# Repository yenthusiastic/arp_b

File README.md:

# Hochschule Rhein-Waal Applied Research Project WS19/20
## Project: Bikota - Distributed ledger-based bike renting system
##### Supervised by Prof. Timo Kahl
##### Group members: Andreas Markwart, Francisco-Alberto Susana-Canela, Thi Yen Thu Nguyen, Sarah-Maria Rostalski, Nader Kaake

### Problem Statement & Market Research 

Bike renting services are re-gaining popularity in many big cities around the world for short distances. Multiple renting services now allow users to conveniently locate vehicles with apps on their smartphone, initiate the renting and returning of a vehicle from and to anywhere unlike with the traditional renting stations.. 
However, current popular bike renting apps such as [Nextbike](https://www.nextbike.de/en/information/), [Lyft](https://www.lyft.com/bikes) or [Uber JUMP](https://www.jump.com/de/de/) require users to register and provide their private payment details. 

This project thus proposes an innovative bike renting service concept based on pseudo-anonymous, registration-free payment using Distributed Ledger Technology, namely [IOTA](https://www.iota.org/get-started/what-is-iota). IOTA is a permissionless, immutable, scalable ledger system that allows for feeless data transaction with or without monetary values. Hence, all data related to any renting session can be anonymously collected, analyzed and utilized for future improvements of the system.

### Methodology 
The architecture of the system (see Fig. 1) can be divided into three main elements, which are: the server that manages our service; the hardware that connects the bike to our platform; and the IOTA Node that processes the payments. Every element communicates with each other through HTTP protocol to process the request from the users and bike administrators. The server consists of three sub-elements or sub-servers which handle a particular task of the renting process such as API calls, data storage and the web platforms.

*Fig. 1: System architecture - BIKOTA Renting System*

### Implementation 
#### Hardware and Firmware
The hardware is based on an ESP32 microcontroller using an E-ink display for user interaction. A SIM800 module provides 2G mobile internet access. The firmware on the ESP32 is developed in the MicroPython programming language. Environmental data like temperature, relative humidity, atmospheric pressure, particulate matter (PM10, PM2.5) and CO2 are measured by multiple sensors. A GPS module provides location data, while an accelerometer is used for automated hardware wake up and vandalism detection.

#### Software 
The software frameworks for the BIKOTA bike renting system are separated into backend and frontend modules. The backend is based on a NodeJS server which implements a RESTful API application for receiving HTTP requests from the hardware modules and sending back responses correspondingly. The data received by the API is saved in a PostgreSQL database and represented visually using the frontend. 

The frontend again consists of two separate user interfaces: a landing page for the common user and a dashboard panel for the admin of the renting system. The web servers are implemented in Python using a Flask framework for web routing and HTTPS request handling.

### Results & Discussion
#### Hardware
The hardware module (see Fig. 2) is able to collect and publish geo-referenced data about its environment, which are sent via 2G to the API application at the backend. Each renting session is handled by the device itself, as the device is checking, if there is a positive balance for an IOTA address and displays the corresponding renting time on the E-ink display. In addition, due to the modular design, it is possible to use the device only for renting and tracking; the environmental sensors are optional.

*Fig. 2: BIKOTA hardware prototype*

#### Software
##### REST API
The REST API accepts the following types of requests from the hardware modules: asking for a new session address, sending sensor data, updating the hardware status. The API returns meaningful HTTP status codes to all requests to indicate whether the requests are successful or erroneous. The complete description of the REST API can be found [here](documentation/REST_API_Server.md).

##### Landing page
The [landing page](http://bikota.xyz) is responsive and can be accessed via computer or mobile phone. It gives the user the opportunity to locate available bikes nearby (see Fig. 3) and gives information about the renting process. After a renting session the user can also view the sensor data, which has been collected during the session, by entering the session address into the interface. The data of the environmental sensors will be displayed as charts and GPS data will be projected to a map.

*Fig. 3: Bike finder section of BIKOTA landing page*

##### Admin Panel
The [admin panel](http://admin.bikota.xyz) allows the admin to have an overview of all hardware modules in the system, including their locations, their status and their usage. The admin can also perform CRUD operations to the PostgreSQL database to create, read, update and delete hardware modules (see Fig. 4). Additionally, any sensor data collected by the hardware modules can also be visualized as graphs for environmental data monitoring. The complete description and usage manual of the admin panel can be found [here](documentation/Admin_Panel_Manual.md).

*Fig. 4: Hardware manager section of BIKOTA admin panel*

### Outlook
This project proposes a proof-of-concept for a bike renting system based on the IOTA ledger. The geo-referenced data as well as sensor data collected from renting sessions are stored and visualized but can be further analyzed for environmental monitoring purposes. For future work, the data can be sent to the IOTA Tangle using Masked Authenticated Messaging protocol to allow customizable distribution channels depending on the use cases, as well as data trading on the [IOTA Data Marketplace](https://data.iota.org/). 
Improvements can also be made to the hardware to automatically make a call or send an SMS once a collision or vandalism is detected to notify the bike owners immediately such that faster actions can be taken.

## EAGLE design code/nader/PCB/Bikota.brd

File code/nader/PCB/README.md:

# PCB development
This readme is going to describe the process of the PCB development. 
It is including the installation and configuration of KiCAD, the electrical and mechanical requirements for the PCB and the design process itself.

## Ideas & plans
The idea of this task is to develop a PCB, which is electrically connecting the single components (MCU, sensors, etc.) together. Most of the sensors are soldered on breakout boards, which include all electrical components necessary for a standard operation. These components are for example resistors, capacitors and/or voltage regulators. Most of the time, a pin header is also included in order to connect the sensor to the MCU using jumper wires.
Breakout boards have also the advantage, that they implicate a very good documentation and that they are easily reusable.
Of course, it is also possible to have a closer look at the breakout boards and use all the necessary components on the main PCB, which is going to be developed. But in order to reduce complexity and the time-stress-level, a PCB using the breakout boards is the way to go.

## Researches

### KiCAD vs. Eagle
The first decision to make is the question of the right PCB design software. The discussions are most of the time endless, but in the end, it is a question of personal preference, as both softwares have their advantages and disadvantages.

#### Price
KiCAD is free and open-source, which means that is possible to download the complete source code and modify it ad libitum. At the other side, EAGLE is available as a free version, but it is restricting the complexity of the projects by three different limitations:
* maximum of two layers
* maximum of two schematics sheets
* maximum of 80 cm² board size

It is also possible to use the full version of EAGLE, but it either costs 17.85 EUR monthly or 130.90 EUR yearly.

#### User interface / User experience
The user interfaces of both softwares are optically not feauturing any major differences, but in terms of user experience, KiCAD is one step ahead by including standard keyboard shortcuts for the different main tools you use when designing a PCB. With Eagle it is possible to use shortcuts, but with the difference, that they have to be configured first. Nevertheless, EAGLE is featuring a command line, where it is possible to type in commands (e.g. wire, place component, etc.). EAGLE's main advtange is that the process of developing a PCB is much more straight-forward, as it takes less steps:
1. Create a schematic
2. Place components. (Here, each time you place a component, you already define the type of footprint you want to choose)
3. Connect the components (circuit)
4. Generate board (one click and the components are placed on the edge of the board)
5. Final placements and connections are made (Changes in the schematics are directly copied in the board)

KiCad involves a few more steps, but after executing these steps multiple times, it does not make a difference. The difference is more decisive for a new-comer.
* The footprints of the components are selected after placing all the components in the schematic.
* Components are not directly named when getting placed
* The process of getting the components and connections to the board involves two more steps
    * Create a netlist
    * Load netlist into the board

#### Components organization
In every PCB design software, each single component is including a *footprint* and a *symbol*; KiCAD and EAGLE are not making any exceptions. The symbol is used when the component is placed in one of the schematics sheets, where rotation and position are not playing any roles. It is only important, that the component is placed and connected to the other components with the *wire tool*. As soon as the schematics are finished, it is time to place the footprint of the component. Here, the position as well as the roation are crucial, as the component is going to be soldered (or fixed) exactly how it is placed in the *Gerber files* (output files of the PCB).
Both softwares have a libary, where you can manage the symbols as well as the footprints, but in my opinion, the one of EAGLE is much more easier to handle. KiCAD is a little bit more complicated (as you can see under *Problems & Troubleshooting*).

### Components
* [LIS3DH](https://www.st.com/resource/en/datasheet/lis3dh.pdf) - Acceleration sensor
* [VIS3590](https://www.reichelt.de/12-mm-magnetischer-buzzer-vis-3590-p248314.html?PROVID=2788&gclid=Cj0KCQiAk7TuBRDQARIsAMRrfUZGc0MFfkMijM4triyhI70YJm8uVk0_bFY5iUcvsQDlfDWVVrutPQUaAqmwEALw_wcB&&r=1) - Buzzer
* [MH-Z14A](https://www.banggood.com/de/NDIR-CO2-Sensor-MH-Z14A-PWM-NDIR-Infrared-Carbon-Dioxide-Sensor-Module-Serial-Port-0-5000PPM-Controller-p-1248270.html?gmcCountry=DE&currency=EUR&createTmp=1&utm_source=googleshopping&utm_medium=cpc_bgs&utm_content=frank&utm_campaign=frank-ssc-de-css-all-19bf11&ad_id=380597671089&gclid=Cj0KCQiAk7TuBRDQARIsAMRrfUZKyH9uKiOI8AsN_9JS3UmNfRLCO_lH9K2vEJEZapdY7mxqP0jCGBUaArfyEALw_wcB&cur_warehouse=CN) - CO₂ sensor
* [BN220](https://www.banggood.com/de/Beitian-BN-220T-GPS-GLONASS-Module-For-APM-Pixhawk-CC3D-Naze32-F3-F4-Flight-Controller-RC-Drone-Airplane-p-1446169.html?gmcCountry=DE&currency=EUR&createTmp=1&utm_source=googleshopping&utm_medium=cpc_bgs&utm_content=frank&utm_campaign=ssc-de-all-0716&ad_id=367212437657&gclid=Cj0KCQiAk7TuBRDQARIsAMRrfUZp8J6SOXBwY3z7kkAh3ZLmuUUmqHAU2cbT82qMtKNmgjt5V-ikGVwaArADEALw_wcB&cur_warehouse=CN) - GPS sensor
* [SDS011](https://www.banggood.com/de/Geekcreit-Nova-PM-Sensor-SDS011-High-Precision-Laser-PM2_5-Air-Quality-Detection-Sensor-Module-Tester-p-1144246.html?gmcCountry=DE&currency=EUR&createTmp=1&utm_source=googleshopping&utm_medium=cpc_bgs&utm_content=frank&utm_campaign=frank-ssc-de-css-all-19bf11&ad_id=380597671089&gclid=Cj0KCQiAk7TuBRDQARIsAMRrfUaDJpclHDIj_aa5fgJSP1aEasOmDeB9t93sI-2GWzTbn4nR9yIGIDQaAoamEALw_wcB&cur_warehouse=CN) - PM sensor
* [RND 135-00180](https://www.reichelt.de/led-smd-0603-blau-200-mcd-rnd-135-00180-p263776.html?&trstct=pol_8) - Status LED
* [BME280](https://www.reichelt.de/entwicklerboards-temperatur-feuchtigkeits-und-drucksensor-debo-sens-thd-p235476.html?&trstct=pos_2) - Temperature, pressure and humidity sensor

## Development of the PCB
In this part, the hardware implementation is going to be outlined. In general, it is the part of the project where all modules with all necessary components are going to be connected to each other on one single place.

### Results
The PCB v0.1 has a final size of 83.69mm by 78.11mm. All sensors are connected to the microcontroller via the PCB, but as all environmental sensors are only used as soon as the bicycle is in use, they are switched on by a mosfet in order to save power. In addition, all the environmental sensors are connected via jumper cables to the board, due to the mounting on the housing because of airflow. 

#### Schematics
The following figure is showing the final schematics of the PCB in version 0.1. 

</br>

The big part in the middle of the schematic is the microcontroller (ESP32) itself. As this PCB is still some kind of a prototype, we have placed socket connector strips next to the connections of the MCU itself in order to have a direct access to all the necessary pins when debugging is necessary. The jumper JP6 is connected to a resistor, which is then directly connected to ground and used for a potential LED. The few components above the microcontroller are used for the buzzer, which is giving an accousting feedback whenever the device is swiched on. Additionally, it can be used to give a general accoustic feedback for different kinds of situations. The three components to the right of the MCU are the three environmental sensors. Above is the measuring the temperature, humidity and the pressure, while the middle one is the CO₂ sensor and below is the sensor used for the measurement of particulate matter in the air. The component in the lower right corner is the ePaper-module, which is displaying the QR-code and general information about the rental itself. Below of the MCU is a voltage divider, which is sent to the sensVN pin of the microcontroller. In the lower left corner is the circuit of the mosfet, which is switching the three environmental sensor on and off. The first component above the mosfet circuit is the voltage regulator including the power socket, which is providing the board with 5V with an input voltage of 3-5V. The GPS module is seen above the voltage regulator, while the last component in the upper left corner is the acceleration sensor itself. The accelerometer is the only sensor, which is soldered directly on the board instead of a connection via jumper wires. 

#### Layout
Once the schematics are finished, the PCB itself has to be designed. All connections are already defined, so it is necessary to place all components in a smart way in order to prevent long traces between two components and also route these traces. The figure below is showing the initial look of the PCB as soon as the file board is generated by the schematics. The yellow lines between the components are representing necessary connections, which have to be routed. In general one can say, that the more chaotic the lines are, the more chaotic is going to be the final routing. 
The first step is to place the components to their final positions, which is shown in the image below. The black area is representing the current dimensions of the PCB. Here, it is very helpful to first group components together. For example, in the schematics it can be seen that the circuit of the mosfet is including the transistor itself, three resistors and an LED. This means, that these components are at the best placed right next to each other. Another example are the spcker connector strips; These have to be placed next to the microcontroller, as its pins are directly connected to those of the sockets. 

</br>

The next figure is showing the PCB after the components have been placed. The power is coming through the connector in the upper left corner. The modules and sensors are placed corresponding to the position of the microcontroller's pins. That's why the ePaper display, the CO₂-Sensor and the GPS module are placed on one side, and the others (Accelerometer, PM-sensor, environmental-sensor and buzzer) are placed on the other side. Furthermore, the mounting houles of the PCB itself have also been placed in the four corners, which fit 3mm mounting screws. 

</br>

The following figure is illustrating the status of the board after the final step. 

</br>

### Problems & Troubleshooting

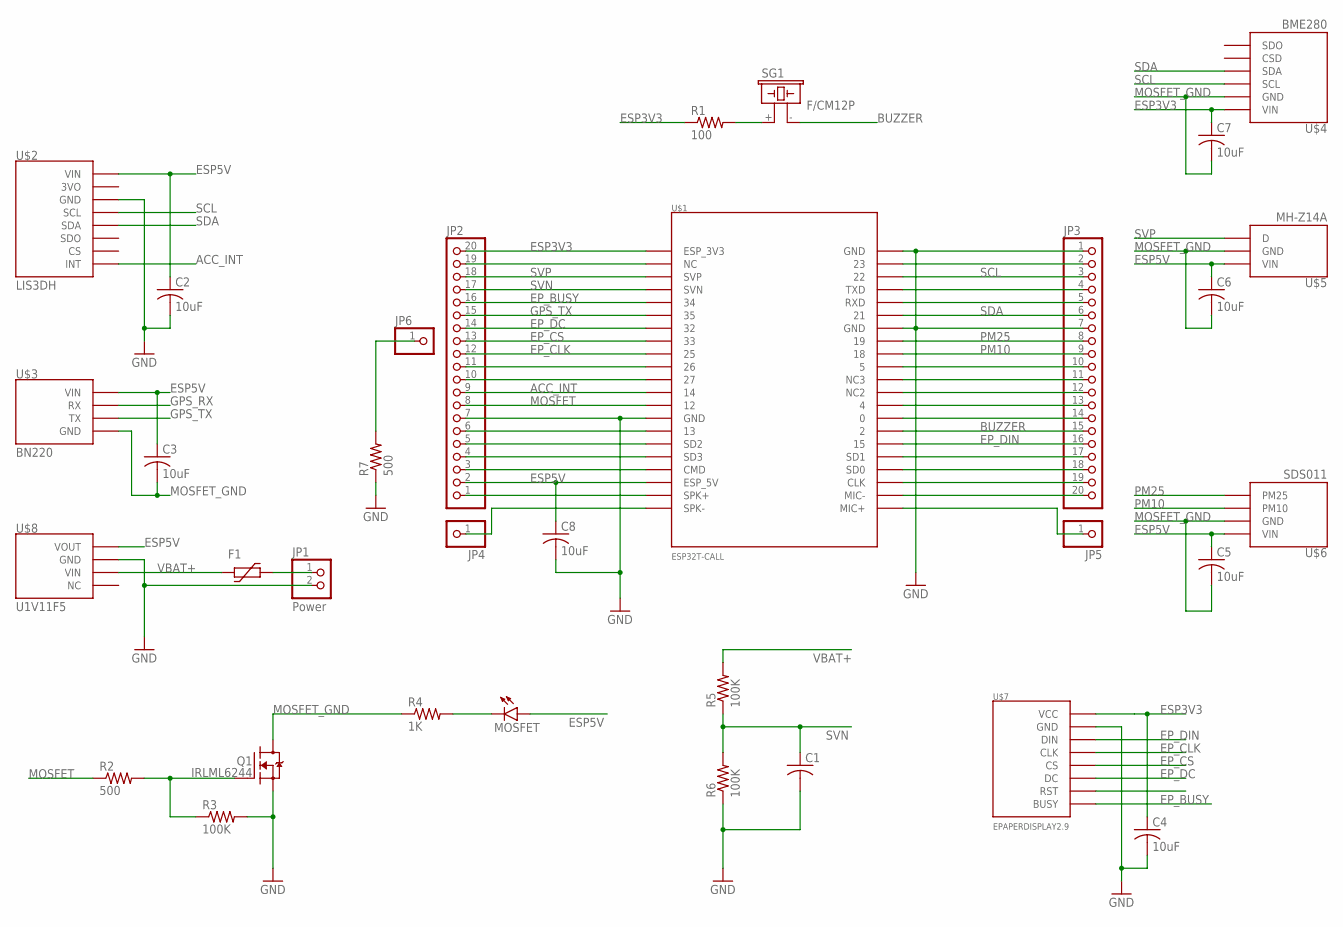
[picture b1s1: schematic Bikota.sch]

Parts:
C1: C-USC0805; C0805
C2, C3, C4, C5, C6, C7, C8: 10uF; C0805
F1: 1206L
JP1: Power; 1X02
JP2, JP3: PINHD-1X20; 1X20
JP4, JP5, JP6: PINHD-1X1; 1X01
MOSFET: LEDCHIPLED_0805; CHIPLED_0805
Q1: IRLML6244; SOT23
R1: 100; R0805
R2, R7: 500; R0805
R3, R5, R6: 100K; R0805
R4: 1K; R0805
SG1: F/CM12P
U$1: ESP32T-CALL
U$2: LIS3DH
U$3: BN220
U$4: BME280
U$5: MH-Z14A
U$6: SDS011
U$7: EPAPERDISPLAY2.9
U$8: U1V11F5

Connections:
3VO: U$2.P$2 (3VO)
ACC_INT: JP2.9, U$1.GPIO14 (14), U$2.P$8 (INT)
BUZZER: JP3.15, SG1.- (2), U$1.GPIO2 (2)
EP_BUSY: JP2.16, U$1.GPIO34 (34), U$7.P$8 (BUSY)
EP_CLK: JP2.12, U$1.GPIO25 (25), U$7.P$4 (CLK)
EP_CS: JP2.13, U$1.GPIO33 (33), U$7.P$5 (CS)
EP_DC: JP2.14, U$1.GPIO32 (32), U$7.P$6 (DC)
EP_DIN: JP3.16, U$1.GPIO15 (15), U$7.P$3 (DIN)
ESP3V3: C4.1, C7.1, JP2.20, R1.1, U$1.ESP32_3V3 (ESP_3V3), U$4.P$1 (VIN), U$7.P$1 (VCC)
ESP5V: C2.1, C3.1, C5.1, C6.1, C8.1, JP2.2, MOSFET.A, U$1.ESP32_5V (ESP_5V), U$2.P$1 (VIN), U$3.P$1 (VIN), U$5.P$1 (VIN), U$6.P$1 (VIN), U$8.P$1 (VOUT)
GND: C1.2, C2.2, C4.2, C8.2, JP1.2, JP2.7, JP3.1, JP3.7, Q1.2 (S), R3.2, R6.1, R7.1, U$1.GND, U$1.GND2 (GND), U$1.GND3 (GND), U$2.P$3 (GND), U$7.P$2 (GND), U$8.P$2 (GND)
GPS_RX: U$3.P$2 (RX)
GPS_TX: JP2.15, U$1.GPIO35 (35), U$3.P$3 (TX)
MOSFET: JP2.8, R2.1, U$1.GPIO12 (12)
MOSFET_GND: C3.2, C5.2, C6.2, C7.2, Q1.3 (D), R4.1, U$3.P$4 (GND), U$4.P$2 (GND), U$5.P$2 (GND), U$6.P$2 (GND)
unnamed: R1.2, SG1.+ (1)
unnamed: JP2.19, U$1.P$2 (NC)
unnamed: Q1.1 (G), R2.2, R3.1
unnamed: MOSFET.C, R4.2
unnamed: JP2.11, U$1.GPIO26 (26)
unnamed: JP2.10, U$1.GPIO27 (27)
unnamed: JP2.6, U$1.GPIO13 (13)
unnamed: JP2.5, U$1.SD2
unnamed: JP2.4, U$1.SD3
unnamed: JP2.3, U$1.CMD
unnamed: JP2.1, U$1.SPK+
unnamed: JP4.1, U$1.SPK-
unnamed: JP6.1, R7.2
unnamed: JP3.2, U$1.GPIO23 (23)
unnamed: JP3.4, U$1.TXD
unnamed: JP3.5, U$1.RXD
unnamed: JP3.10, U$1.GPIO5 (5)
unnamed: JP3.11, U$1.NC3
unnamed: JP3.12, U$1.NC2
unnamed: JP3.13, U$1.GPIO4 (4)
unnamed: JP3.14, U$1.GPIO0 (0)
unnamed: JP3.17, U$1.SD1
unnamed: JP3.18, U$1.SD0
unnamed: JP3.19, U$1.CLK
unnamed: JP3.20, U$1.MIC-
unnamed: JP5.1, U$1.MIC+
unnamed: F1.P$2 (2), JP1.1
PM10: JP3.9, U$1.GPIO18 (18), U$6.P$3 (PM10)
PM25: JP3.8, U$1.GPIO19 (19), U$6.P$4 (PM25)
SCL: JP3.3, U$1.GPIO22 (22), U$2.P$4 (SCL), U$4.P$3 (SCL)
SDA: JP3.6, U$1.GPIO21 (21), U$2.P$5 (SDA), U$4.P$4 (SDA)
SVN: C1.1, JP2.17, R5.1, R6.2, U$1.SVN
SVP: JP2.18, U$1.SVP, U$5.P$3 (D)
VBAT+: F1.P$1 (1), R5.2, U$8.P$3 (VIN)

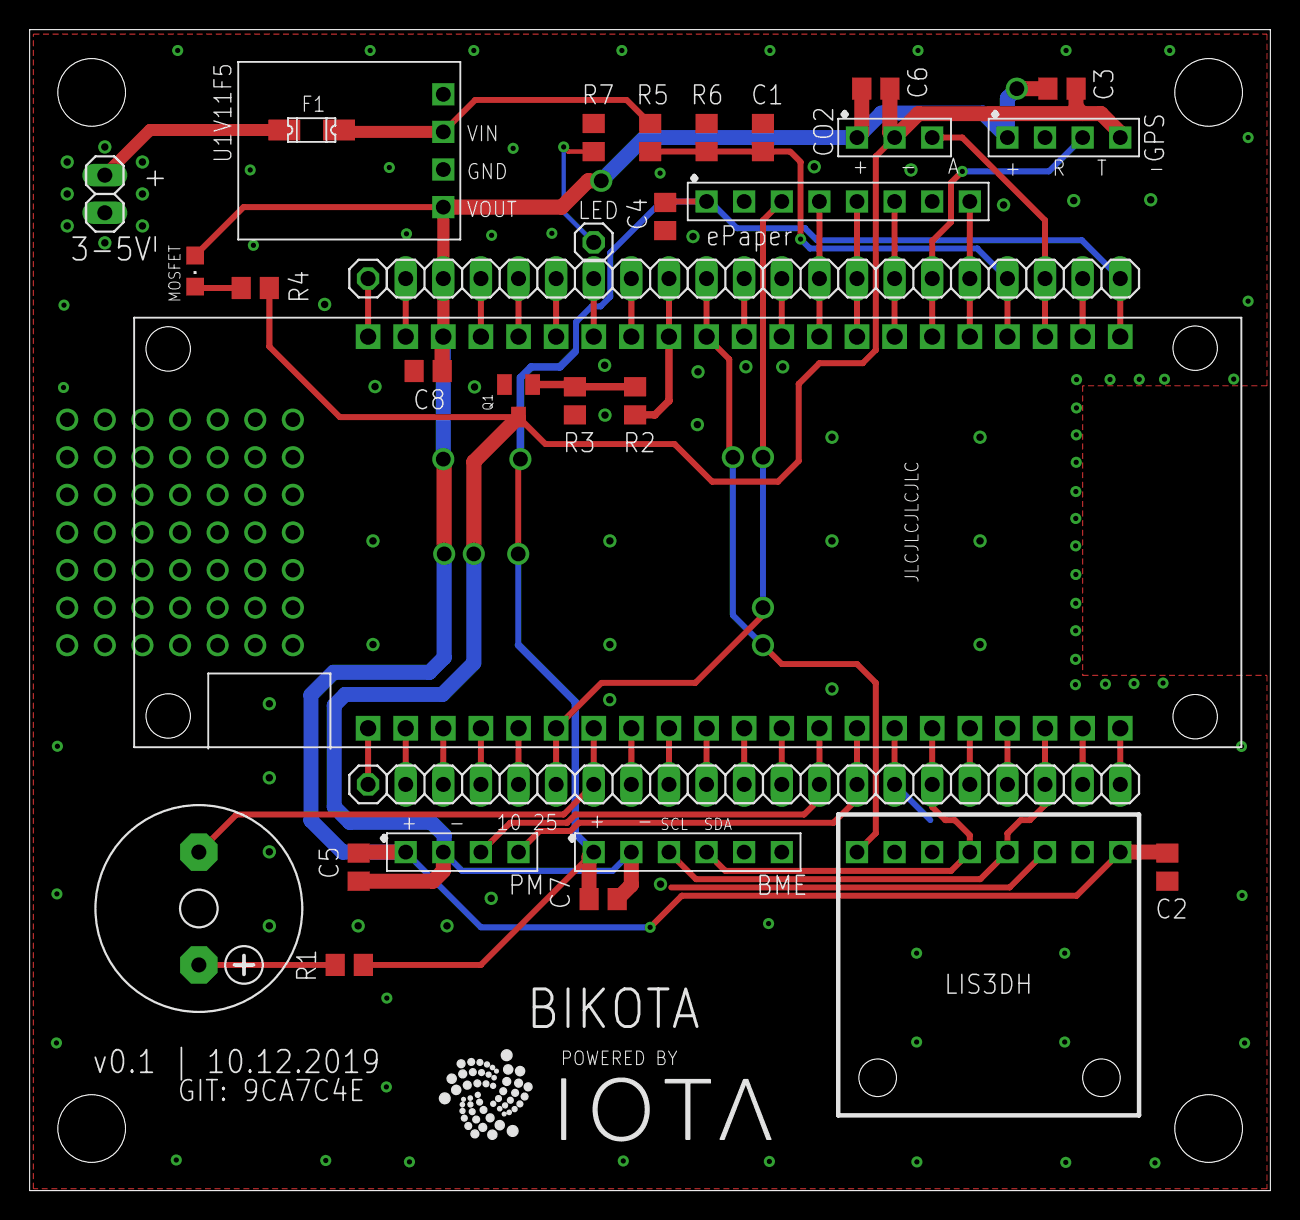
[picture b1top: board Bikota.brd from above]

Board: 2 copper layers, 83.8 x 78.4 mm, 33 parts (0 on the bottom side), 47 nets.

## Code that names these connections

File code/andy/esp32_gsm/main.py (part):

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

# Accelerometer Interrupt wake-up pin
acc_int = Pin(14, Pin.IN, Pin.PULL_DOWN)

# wake-up source for deepsleep
#rtc.wake_on_ext0(pin=btn1, level=0) #wakeup at btn low
rtc.wake_on_ext0(pin=acc_int, level=1) # wakeup at acc_int high

# MOSFET for 5V AUX
mos = Pin(12, Pin.OUT, value=0)
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

# PM sensor, SDS011
PM10_PIN = Pin(19, Pin.IN)
PM25_PIN = Pin(18, Pin.IN)


# Turn on auxiliary sensors
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    

"""
def get_pm(p10=PM10_PIN, p25=PM25_PIN):
    while p10.value() !=0:
        sleep_ms(1)
    while p10.value() == 0:
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"""

if SENSOR_MODE:
    def get_pm(p10=PM10_PIN, p25=PM25_PIN):
        while p10.value() == 0:
            pass
        st_10=ticks_ms()
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
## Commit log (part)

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2019-09-22 make directories
2019-09-22 make sub directories for each member's code
2019-09-22 add documentation for dev-server
2019-09-23 add gsm-module control, add RTC setup by NTP, fix get_balance()
2019-09-24 update Concept
2019-09-24 add directory 'sensors'
2019-09-24 add list of sensors to 'hardware'
2019-09-24 update esp32 modem and low-power operation documentation
2019-09-25 update power measurements
2019-09-25 update flashing instructions
2019-09-25 [thu] update to-dos list
2019-09-27 add function to send IOTA transaction containing sensor data from API server to IOTA node
2019-09-29 server file name update
2019-09-30 update documentation for API and DB requirements
2019-09-30 add main.py
2019-10-01 add arduino_gsm example
2019-10-01 update MicroPython binaries
2019-10-01 add AT-command based SIM800 library - in development
2019-10-06 add micropython at-command version
2019-10-06 refractor ESP32 code
2019-10-07 add new sub folders for members
2019-10-08 add sds011 library
2019-10-08 add sensor datasheets
2019-10-12 add DHT22, GPIO cleanup, test deepsleep wakeup
2019-10-12 add flask-dashboard template
2019-10-12 update postgres image to version 12
2019-10-12 Update API_DB_structure.md
    Correct database name.
2019-10-13 REST API V1.0, get & post http request
2019-10-14 Error handling added as described in API_DB_Structure.
2019-10-14 add library for QR code generation
2019-10-14 add display output, qr-code generation, mpu6050
2019-10-15 update info on messagepack
2019-10-16 modify mpu6050 library
2019-10-16 integrade epaper display
2019-10-17 Update app.js and queries.js files
2019-10-17 catch updated to catch(e)
2019-10-17 add notes for virtual environment
2019-10-17 Rquest update
2019-10-17 1.1-Fixing API response to python request
2019-10-18 modify for new b/w only e-paper
2019-10-18 add library for b/w only e-paper
2019-10-21 add functions for display update rate testing
2019-10-22 add MPU6050 datasheets
2019-10-24 add MZ-14 CO2 sensor
2019-10-30 add mpu6050 example for esp32 with oled
2019-10-31 add authentication and profile for admin interface
2019-10-31 add notifications for admin page
2019-11-01 add form controls for chart customization
2019-11-03 add more UI controls for web admin interface
    - add Date/Time Range Picker
    - allow multiple series per chart
2019-11-03 dynamic generation of charts based on user 's input
    - allow mutiple charts and mutilple series per chart to be plotted based on user's selections
    - TO DO: fix problem with slow database communication
2019-11-03 add BME280 library
2019-11-03 integrate BME280
2019-11-07 add toggle for editing modes, use bootstrap select library for dropdown menus
2019-11-09 add MOSFET and buzzer, add RTC-memory handling for status and address, streamline startup process, add startup sound
2019-11-10 save session_address and qr-code to RTC-memory and load at wakeup
2019-11-11 [Web UI] add new page for hardware manager
2019-11-12 finish basic hardware manager page
2019-11-14 Initial update
    - Sourcecode of the logical connection of MCU and Accelerometer (interrupts not working yet)
    - Driver for ESP32 (Win10)
    - ReadMe of the PCB development
2019-11-14 Delete README.md
    Separate READMEs in their specific folders
2019-11-17 Added Arduino Sketch File
    Interrupt configuration using the LIS3DH acceleration sensor.
    + interrupts are working and configurations settings are well tuned (thresholds, duration, etc.)
    - Wake-Up missing
2019-11-17 Update LIS3DH_INT.ino
    Added comments
2019-11-18 folder name update
2019-11-18 update package.json files
2019-11-18 Update comments and port var
2019-11-23 Status code for POST and PUT updated
2019-11-26 iota-api program to generate, and verify an address, and connect to test node
2019-11-28 fix Admin Panel bugs, create usage manual document
2019-11-29 update documentation for admin panel
2019-12-01 implement map page to show bike distribution
2019-12-01 update co2 sensor datasheet
2019-12-01 update documentation
2019-12-03 Added lis3dh file
    Driver and interrupt settings (accceleration values not available)
2019-12-06 Uploaded first version of the PCB
    Including Libraries and ULP to automatically create rectangles
2019-12-07 Added additional libraries
    Bikota.lbr is replacing lis3dh.lbr
2019-12-07 Updated schematic and board files.
2019-12-08 Refractoring: add constants
2019-12-08 Endpoints updated and IOTA-API integrated to generate seed and session address.
2019-12-08 app.js renamed and query-address.js logs display improved.
2019-12-08 Update on generate-seed.js the var 'randomValues' to Uint32Array
2019-12-09 Session_address added to the response on the query-address.
2019-12-09 Update PCB and SCH
2019-12-11 fix hardware.html to handle null data
2019-12-12 Update V0.1
    - put "3-5V" below the input socket
    - named the mosfet-led "MOSFET" instead of "LED1"
2019-12-12 Upload Gerber files
2019-12-13 Upload img of schematics
2019-12-13 Added images of the board
2019-12-21 RESTAPI: enable new hardware address query request.
2019-12-22 RESTAPI: code refactoring.
2019-12-22 lis3dh.py updated
    Changed/corrected functions to write registers of the accelerometer
2020-01-04 add get_address function; add LIS3DH Sensor; add battery voltage reading; fix parking and balance_update countdown
2020-01-04 add gitignore for code/andy
2020-01-05 add data aggregation function to chart page
2020-01-05 add wake-up by LIS3DH interrupt; add demo mode for session; streamline first boot
2020-01-06 RESTAPI: Code refactoring to optimize API routes and DB connection.
2020-01-06 show last sensor data on map
2020-01-08 Uploaded an image of the board
2020-01-09 add SENSOR_MODE flag for environmental sensors; add watchdog resets; fix backend keyword change
2020-01-12 Bump werkzeug from 0.14.1 to 0.15.3 in /code/thu/flask-dashboard
    Bumps [werkzeug](https://github.com/pallets/werkzeug) from 0.14.1 to 0.15.3.
    - [Release notes](https://github.com/pallets/werkzeug/releases)
    - [Changelog](https://github.com/pallets/werkzeug/blob/master/CHANGES.rst)
    - [Commits](https://github.com/pallets/werkzeug/compare/0.14.1...0.15.3)
2020-01-12 RESTAPI: add README file.
2020-01-12 RESTAPI: Fix readme file format.
2020-01-13 RESTAPI: Node status integration update.
2020-01-15 edit aggregation logic for chart data, fix JS logic for chart control dropdown menus
2020-01-16 RESTAPI: router update and data-post fixed.
2020-01-19 Webpage for user
2020-02-13 RESTAPI: readme update.
2020-02-13 update libraries
2020-02-14 REST API: README update.
2020-02-28 README update
2020-08-20 Bump bcrypt from 3.0.6 to 5.0.0 in /code/francisco/rest_api_server
    Bumps [bcrypt](https://github.com/kelektiv/node.bcrypt.js) from 3.0.6 to 5.0.0.
    - [Release notes](https://github.com/kelektiv/node.bcrypt.js/releases)
    - [Changelog](https://github.com/kelektiv/node.bcrypt.js/blob/master/CHANGELOG.md)
    - [Commits](https://github.com/kelektiv/node.bcrypt.js/compare/v3.0.6...v5.0.0)
2021-04-30 Bump urllib3 from 1.25.7 to 1.25.8 in /code/thu/flask-dashboard
    Bumps [urllib3](https://github.com/urllib3/urllib3) from 1.25.7 to 1.25.8.
    - [Release notes](https://github.com/urllib3/urllib3/releases)
    - [Changelog](https://github.com/urllib3/urllib3/blob/main/CHANGES.rst)
    - [Commits](https://github.com/urllib3/urllib3/compare/1.25.7...1.25.8)
2021-05-06 Bump flask-cors from 3.0.7 to 3.0.9 in /code/thu/flask-dashboard
    Bumps [flask-cors](https://github.com/corydolphin/flask-cors) from 3.0.7 to 3.0.9.
    - [Release notes](https://github.com/corydolphin/flask-cors/releases)
    - [Changelog](https://github.com/corydolphin/flask-cors/blob/master/CHANGELOG.md)
    - [Commits](https://github.com/corydolphin/flask-cors/compare/3.0.7...3.0.9)
2021-06-02 Bump urllib3 from 1.25.7 to 1.26.5 in /code/thu/flask-dashboard
    Bumps [urllib3](https://github.com/urllib3/urllib3) from 1.25.7 to 1.26.5.
    - [Release notes](https://github.com/urllib3/urllib3/releases)
    - [Changelog](https://github.com/urllib3/urllib3/blob/main/CHANGES.rst)
    - [Commits](https://github.com/urllib3/urllib3/compare/1.25.7...1.26.5)
    ---
    updated-dependencies:
2021-10-06 Bump url-parse from 1.4.7 to 1.5.3 in /code/francisco/rest_api_server
    Bumps [url-parse](https://github.com/unshiftio/url-parse) from 1.4.7 to 1.5.3.
    - [Release notes](https://github.com/unshiftio/url-parse/releases)
    - [Commits](https://github.com/unshiftio/url-parse/compare/1.4.7...1.5.3)
    ---
    updated-dependencies:
    - dependency-name: url-parse
2022-02-10 Bump undefsafe from 2.0.2 to 2.0.5 in /code/francisco/rest_api_server
    Bumps [undefsafe](https://github.com/remy/undefsafe) from 2.0.2 to 2.0.5.
    - [Release notes](https://github.com/remy/undefsafe/releases)
    - [Commits](https://github.com/remy/undefsafe/compare/v2.0.2...v2.0.5)
    ---
    updated-dependencies:
    - dependency-name: undefsafe
2022-02-18 Bump url-parse from 1.4.7 to 1.5.7 in /code/francisco/rest_api_server
    Bumps [url-parse](https://github.com/unshiftio/url-parse) from 1.4.7 to 1.5.7.
    - [Release notes](https://github.com/unshiftio/url-parse/releases)
    - [Commits](https://github.com/unshiftio/url-parse/compare/1.4.7...1.5.7)
    ---
    updated-dependencies:
    - dependency-name: url-parse
2022-03-29 Bump paramiko from 2.6.0 to 2.10.1 in /code/thu/flask-dashboard
    Bumps [paramiko](https://github.com/paramiko/paramiko) from 2.6.0 to 2.10.1.
    - [Release notes](https://github.com/paramiko/paramiko/releases)
    - [Changelog](https://github.com/paramiko/paramiko/blob/main/NEWS)
    - [Commits](https://github.com/paramiko/paramiko/compare/2.6.0...2.10.1)
    ---
    updated-dependencies:
2022-04-28 Bump cross-fetch from 3.0.4 to 3.1.5 in /code/francisco/rest_api_server
    Bumps [cross-fetch](https://github.com/lquixada/cross-fetch) from 3.0.4 to 3.1.5.
    - [Release notes](https://github.com/lquixada/cross-fetch/releases)
    - [Commits](https://github.com/lquixada/cross-fetch/compare/v3.0.4...v3.1.5)
    ---
    updated-dependencies:
    - dependency-name: cross-fetch
2022-09-16 Bump mako from 1.1.0 to 1.2.2 in /code/thu/flask-dashboard
    Bumps [mako](https://github.com/sqlalchemy/mako) from 1.1.0 to 1.2.2.
    - [Release notes](https://github.com/sqlalchemy/mako/releases)
    - [Changelog](https://github.com/sqlalchemy/mako/blob/main/CHANGES)
    - [Commits](https://github.com/sqlalchemy/mako/commits)
    ---
    updated-dependencies:
2022-12-07 Bump qs, body-parser and express in /code/francisco/rest_api_server
    Bumps [qs](https://github.com/ljharb/qs) to 6.11.0 and updates ancestor dependencies [qs](https://github.com/ljharb/qs), [body-parser](https://github.com/expressjs/body-parser) and [express](https://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
    Updates `qs` from 6.7.0 to 6.11.0
    - [Release notes](https://github.com/ljharb/qs/releases)
    - [Changelog](https://github.com/ljharb/qs/blob/main/CHANGELOG.md)
    - [Commits](https://github.com/ljharb/qs/compare/v6.7.0...v6.11.0)
    Updates `body-parser` from 1.19.0 to 1.20.1
2022-12-08 Bump certifi from 2019.9.11 to 2022.12.7 in /code/thu/flask-dashboard
    Bumps [certifi](https://github.com/certifi/python-certifi) from 2019.9.11 to 2022.12.7.
    - [Release notes](https://github.com/certifi/python-certifi/releases)
    - [Commits](https://github.com/certifi/python-certifi/compare/2019.09.11...2022.12.07)
    ---
    updated-dependencies:
    - dependency-name: certifi
2022-12-26 Bump wheel from 0.33.6 to 0.38.1 in /code/thu/flask-dashboard
    Bumps [wheel](https://github.com/pypa/wheel) from 0.33.6 to 0.38.1.
    - [Release notes](https://github.com/pypa/wheel/releases)
    - [Changelog](https://github.com/pypa/wheel/blob/main/docs/news.rst)
    - [Commits](https://github.com/pypa/wheel/compare/0.33.6...0.38.1)
    ---
    updated-dependencies:
